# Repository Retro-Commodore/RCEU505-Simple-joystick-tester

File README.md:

# RCEU505 - Simple Joysticktester
A Simple Joystick Tester as a DIY for Commodore/Atari style digital joystick

Read the document for which resistor values to use for which color LED.  
The LED's can be generic ones from eBay, so resistor values might not be right for your choice.  

Shopping list
* 5x resistors
* 5x 5mm round LEDs
* 1x 9 pin sub-d male
* 1x CR2032 socket
* 1x CR20xx battery (CR2016/CR2025/CR2032 have been tested in the sockets)

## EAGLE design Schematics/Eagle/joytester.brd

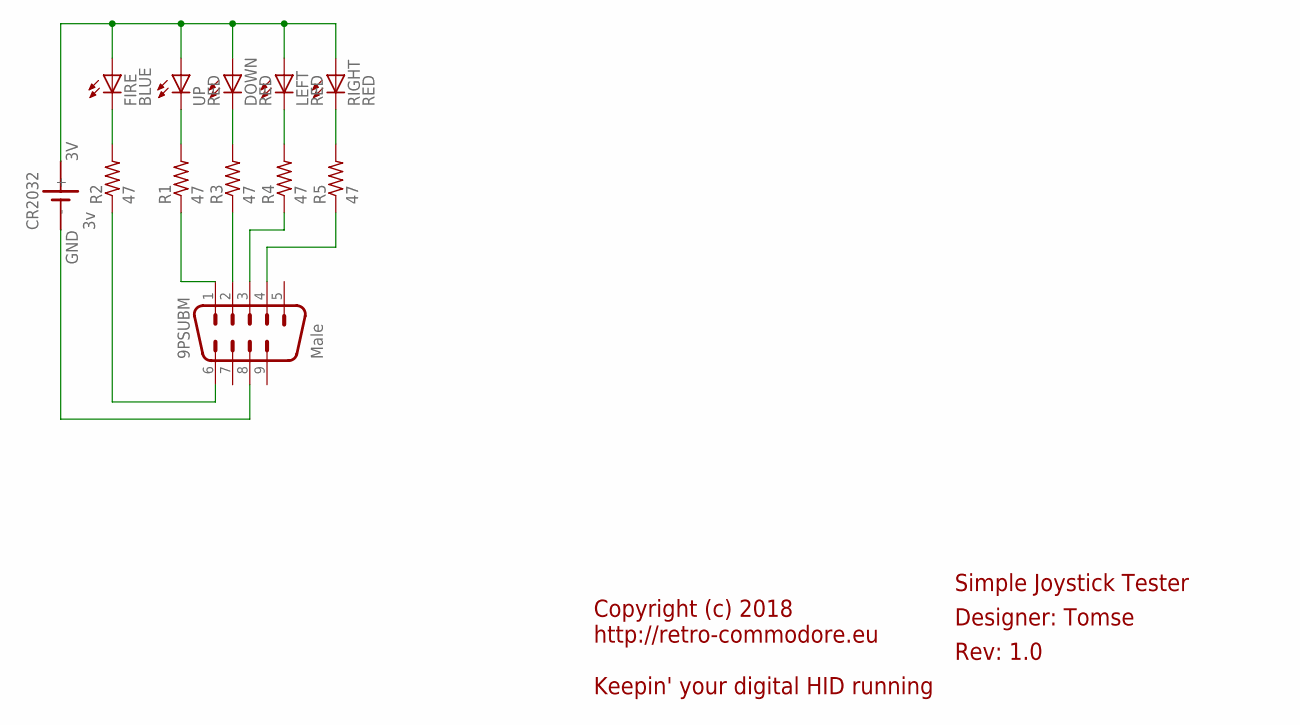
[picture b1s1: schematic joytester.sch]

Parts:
9PSUBM: Male; M09D
CR2032: 3v; SN2032
DOWN: RED; LED5MM
FIRE: BLUE; LED5MM
LEFT: RED; LED5MM
R1, R2, R3, R4, R5: 47; 0207/12
RIGHT: RED; LED5MM
UP: RED; LED5MM

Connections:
3V: CR2032.+, DOWN.A, FIRE.A, LEFT.A, RIGHT.A, UP.A
DOWN: 9PSUBM.2, R3.1
GND: 9PSUBM.8, CR2032.-
unnamed: FIRE.K (C), R2.2
unnamed: LEFT.K (C), R4.2
unnamed: R5.2, RIGHT.K (C)
unnamed: R1.2, UP.K (C)
unnamed: DOWN.K (C), R3.2
unnamed: 9PSUBM.6, R2.1
unnamed: 9PSUBM.3, R4.1
unnamed: 9PSUBM.4, R5.1
UP: 9PSUBM.1, R1.1

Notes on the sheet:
Copyright (c) 2018 http://retro-commodore.eu Keepin' your digital HID running
Simple Joystick Tester
Designer: Tomse
Rev: 1.0

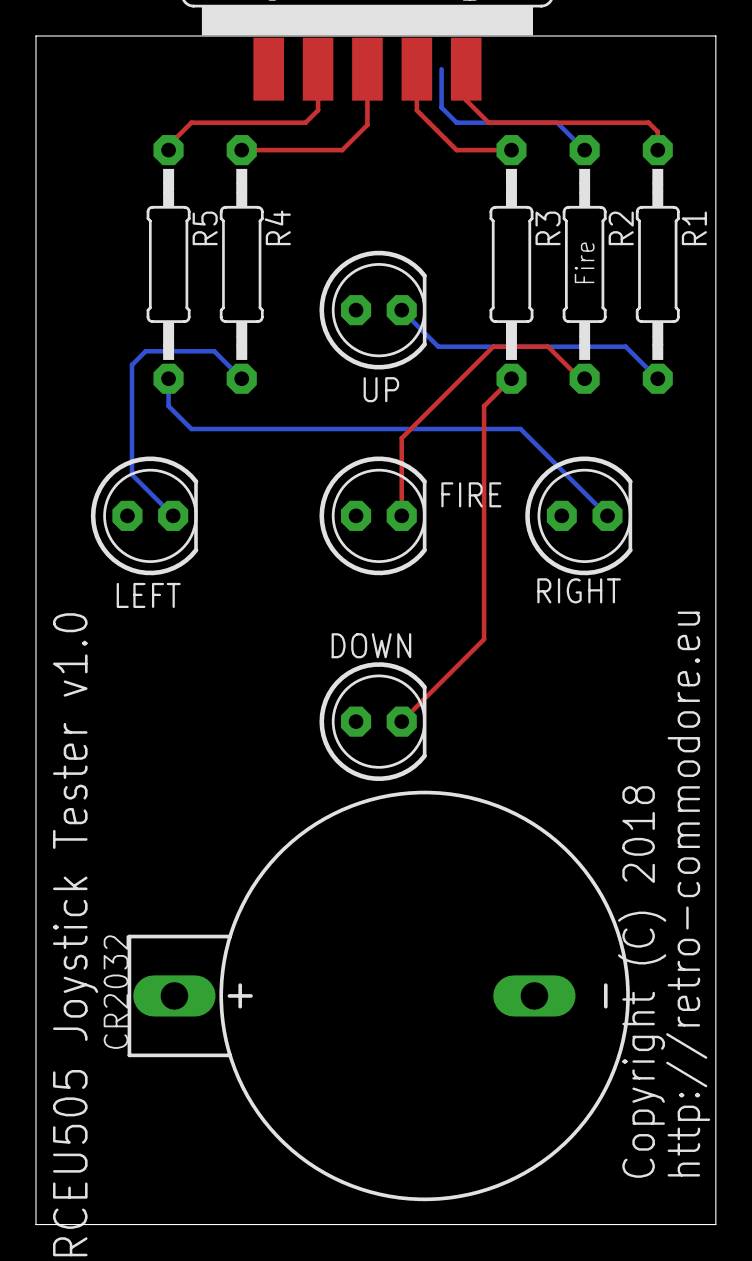
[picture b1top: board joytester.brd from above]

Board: 2 copper layers, 37.8 x 66.0 mm, 12 parts (0 on the bottom side), 12 nets.

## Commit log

2018-10-09 Update LICENSE
2020-04-06 cosmetic changes
2020-04-06 Fixing dirnaming
2020-09-27 moved to kicad, while adding support for joystick button nr 2
2020-09-27 Clean up
2021-01-17 Cosmetic changed - added 3d components to 3d view
